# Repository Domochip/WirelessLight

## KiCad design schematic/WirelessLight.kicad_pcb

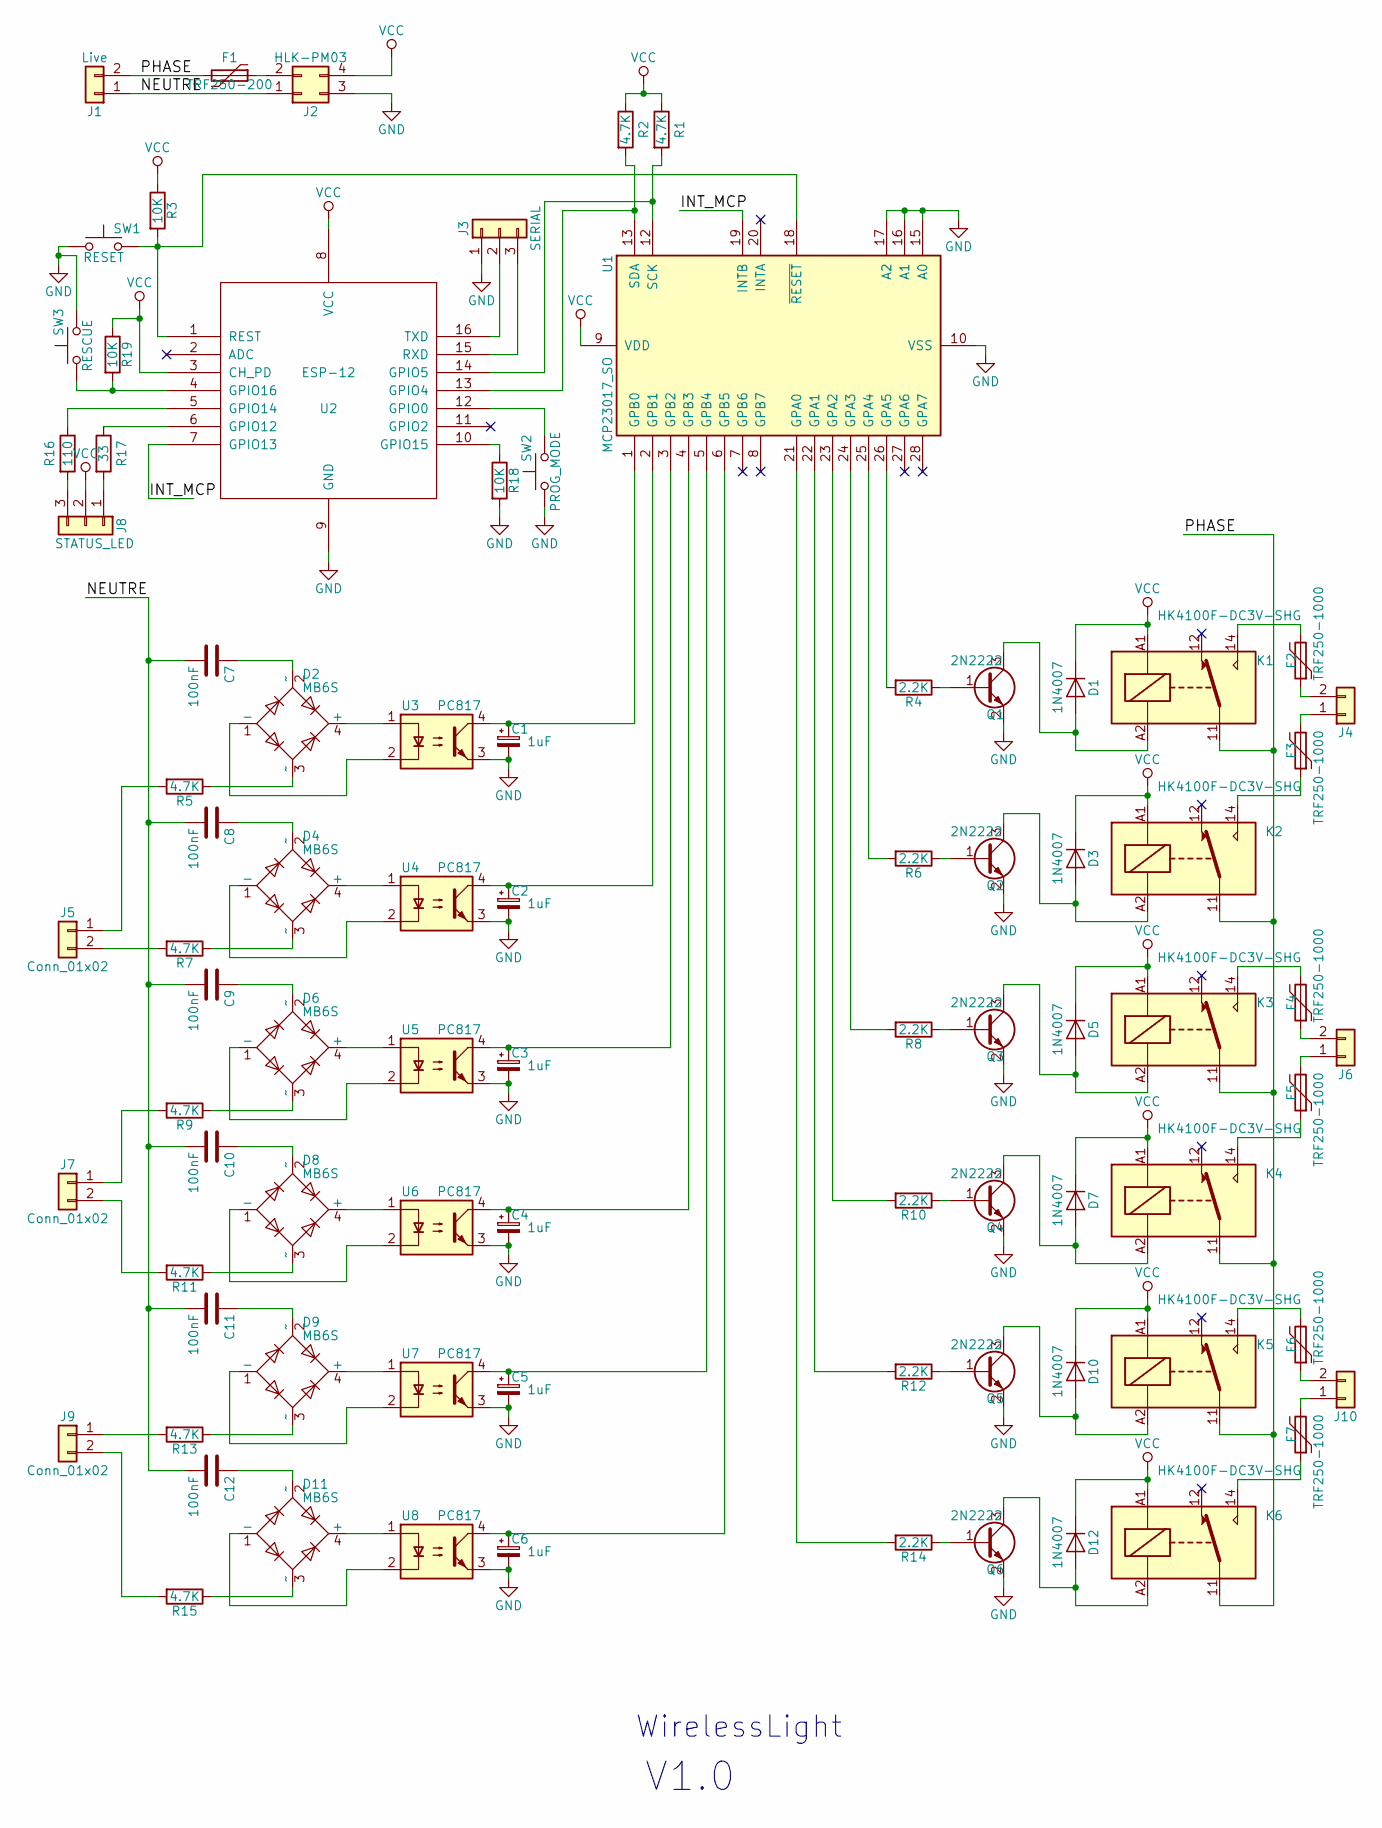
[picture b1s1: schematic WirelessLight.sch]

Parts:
C1, C2, C3, C4, C5, C6: 1uF; C_0805_HandSoldering
C7, C8, C9, C10, C11, C12: 100nF; C_1812_HandSoldering
D1, D3, D5, D7, D10, D12: 1N4007; D_SMA_Handsoldering
D2, D4, D6, D8, D9, D11: MB6S; TO-269AA
F1: TRF250-200; TRF250-400
F2, F3, F4, F5, F6, F7: TRF250-1000
J1: Live; KF235-2P-3.81
J2: HLK-PM03; HLK-PM01
J3: SERIAL; Pin_Header_Straight_1x03_Pitch2.54mm
J4, J5, J6, J7, J9, J10: Conn_01x02; KF235-2P-3.81
J8: STATUS_LED; Pin_Header_Straight_1x03_Pitch2.54mm
K1, K2, K3, K4, K5, K6: HK4100F-DC3V-SHG; HK4100F
Q1, Q2, Q3, Q4, Q5, Q6: 2N2222; SOT-23_Handsoldering
R1, R2: 4.7K; R_0805_HandSoldering
R3, R18, R19: 10K; R_0805_HandSoldering
R4, R6, R8, R10, R12, R14: 2.2K; R_0805_HandSoldering
R5, R7, R9, R11, R13, R15: 4.7K; R_2010_HandSoldering
R16: 110; R_0805_HandSoldering
R17: 33; R_0805_HandSoldering
SW1: RESET; SW_PUSH_6mm_h5mm
SW2: PROG_MODE; SW_PUSH_6mm_h5mm
SW3: RESCUE; SW_PUSH_6mm_h5mm
U1: MCP23017_SO; SOIC-28W_7.5x17.9mm_Pitch1.27mm
U2: ESP-12
U3, U4, U5, U6, U7, U8: PC817; DIP-4_W8.89mm_SMDSocket_LongPads

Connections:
/INT_MCP: U1.19 (INTB), U2.7 (GPIO13)
/NEUTRE: C7.2, C8.2, C9.2, C10.2, C11.2, C12.2, J1.1, J2.1
/PHASE: F1.2, J1.2, K1.11, K2.11, K3.11, K4.11, K5.11, K6.11
GND: C1.2, C2.2, C3.2, C4.2, C5.2, C6.2, J2.3, J3.1, Q1.2 (E), Q2.2 (E), Q3.2 (E), Q4.2 (E), Q5.2 (E), Q6.2 (E), R18.2, SW1.1, SW2.1, SW3.2, U1.10 (VSS), U1.15 (A0), U1.16 (A1), U1.17 (A2), U2.9 (GND), U3.3, U4.3, U5.3, U6.3, U7.3, U8.3
unnamed: C1.1, U1.1 (GPB0), U3.4
unnamed: C2.1, U1.2 (GPB1), U4.4
unnamed: C3.1, U1.3 (GPB2), U5.4
unnamed: C4.1, U1.4 (GPB3), U6.4
unnamed: C5.1, U1.5 (GPB4), U7.4
unnamed: C6.1, U1.6 (GPB5), U8.4
unnamed: C7.1, D2.2 (~~)
unnamed: C8.1, D4.2 (~~)
unnamed: C9.1, D6.2 (~~)
unnamed: C10.1, D8.2 (~~)
unnamed: C11.1, D9.2 (~~)
unnamed: C12.1, D11.2 (~~)
unnamed: D1.2 (A), K1.A2, Q1.3 (C)
unnamed: D2.1 (-), U3.2
unnamed: D2.3 (~~), R5.1
unnamed: D2.4 (+), U3.1
unnamed: D3.2 (A), K2.A2, Q2.3 (C)
unnamed: D4.1 (-), U4.2
unnamed: D4.3 (~~), R7.1
unnamed: D4.4 (+), U4.1
unnamed: D5.2 (A), K3.A2, Q3.3 (C)
unnamed: D6.1 (-), U5.2
unnamed: D6.3 (~~), R9.1
unnamed: D6.4 (+), U5.1
unnamed: D7.2 (A), K4.A2, Q4.3 (C)
unnamed: D8.1 (-), U6.2
unnamed: D8.3 (~~), R11.1
unnamed: D8.4 (+), U6.1
unnamed: D9.1 (-), U7.2
unnamed: D9.3 (~~), R13.1
unnamed: D9.4 (+), U7.1
unnamed: D10.2 (A), K5.A2, Q5.3 (C)
unnamed: D11.1 (-), U8.2
unnamed: D11.3 (~~), R15.1
unnamed: D11.4 (+), U8.1
unnamed: D12.2 (A), K6.A2, Q6.3 (C)
unnamed: F1.1, J2.2
unnamed: F2.1, J4.2
unnamed: F2.2, K1.14
unnamed: F3.1, K2.14
unnamed: F3.2, J4.1
unnamed: F4.1, J6.2
unnamed: F4.2, K3.14
unnamed: F5.1, K4.14
unnamed: F5.2, J6.1
unnamed: F6.1, J10.2
unnamed: F6.2, K5.14
unnamed: F7.1, K6.14
unnamed: F7.2, J10.1
unnamed: J3.2, U2.16 (TXD)
unnamed: J3.3, U2.15 (RXD)
unnamed: J5.1, R5.2
unnamed: J5.2, R7.2
unnamed: J7.1, R9.2
unnamed: J7.2, R11.2
unnamed: J8.1, R17.2
unnamed: J8.3, R16.2
unnamed: J9.1, R13.2
unnamed: J9.2, R15.2
unnamed: Q1.1 (B), R4.1
unnamed: Q2.1 (B), R6.1
unnamed: Q3.1 (B), R8.1
unnamed: Q4.1 (B), R10.1
unnamed: Q5.1 (B), R12.1
unnamed: Q6.1 (B), R14.1
unnamed: R1.2, U1.12 (SCK), U2.14 (GPIO5)
unnamed: R2.2, U1.13 (SDA), U2.13 (GPIO4)
unnamed: R3.2, SW1.2, U1.18 (~RESET~), U2.1 (REST)
unnamed: R4.2, U1.26 (GPA5)
unnamed: R6.2, U1.25 (GPA4)
unnamed: R8.2, U1.24 (GPA3)
unnamed: R10.2, U1.23 (GPA2)
unnamed: R12.2, U1.22 (GPA1)
unnamed: R14.2, U1.21 (GPA0)
unnamed: R16.1, U2.5 (GPIO14)
unnamed: R17.1, U2.6 (GPIO12)
unnamed: R18.1, U2.10 (GPIO15)
unnamed: R19.2, SW3.1, U2.4 (GPIO16)
unnamed: SW2.2, U2.12 (GPIO0)
VCC: D1.1 (K), D3.1 (K), D5.1 (K), D7.1 (K), D10.1 (K), D12.1 (K), J2.4, J8.2, K1.A1, K2.A1, K3.A1, K4.A1, K5.A1, K6.A1, R1.1, R2.1, R3.1, R19.1, U1.9 (VDD), U2.3 (CH_PD), U2.8 (VCC)

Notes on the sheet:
WirelessLight
V1.0

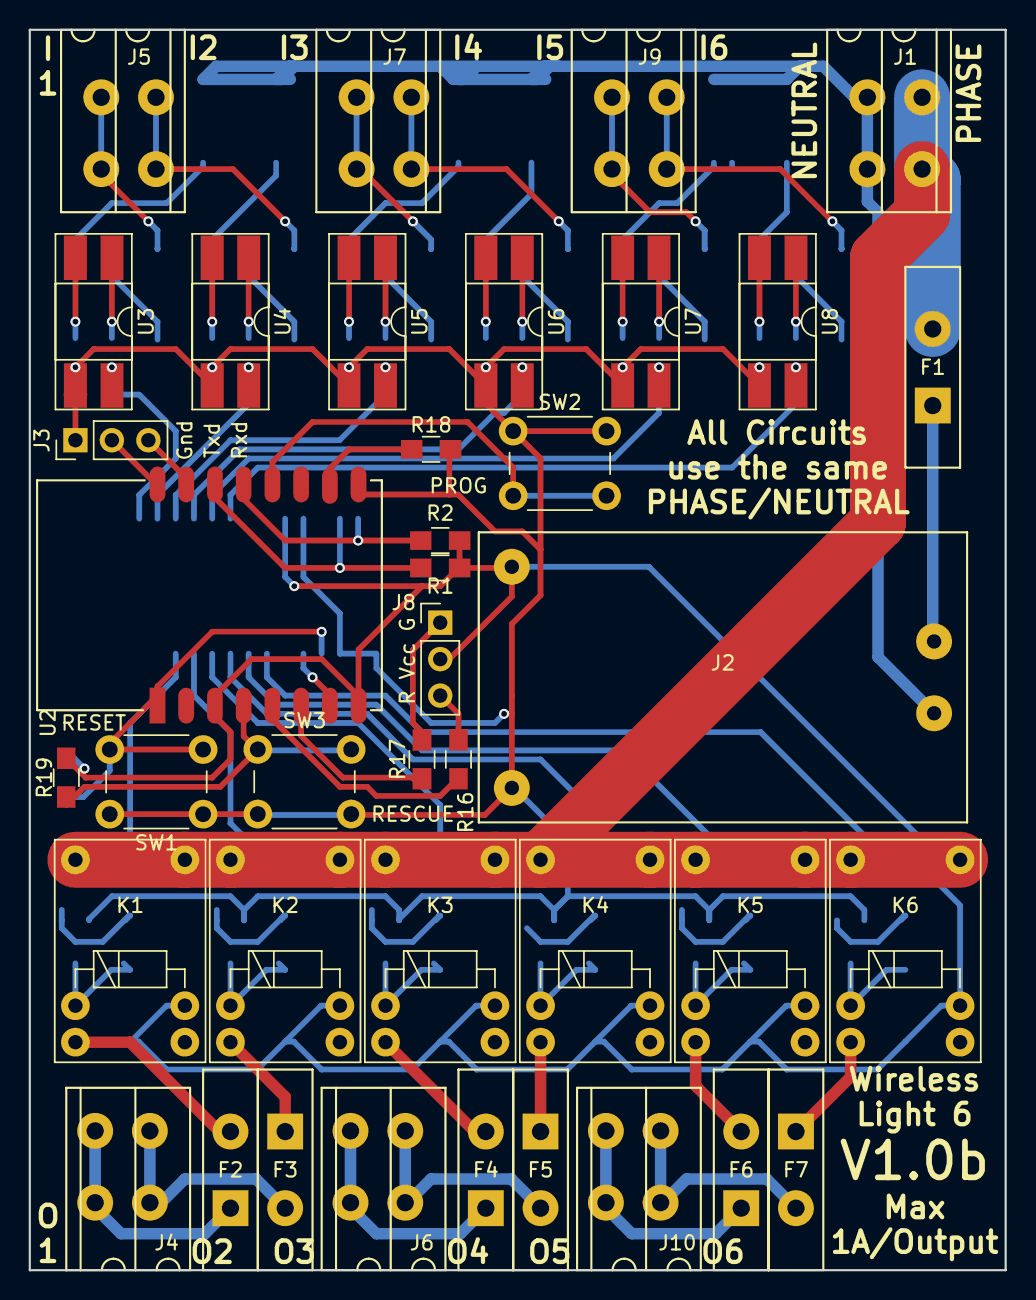
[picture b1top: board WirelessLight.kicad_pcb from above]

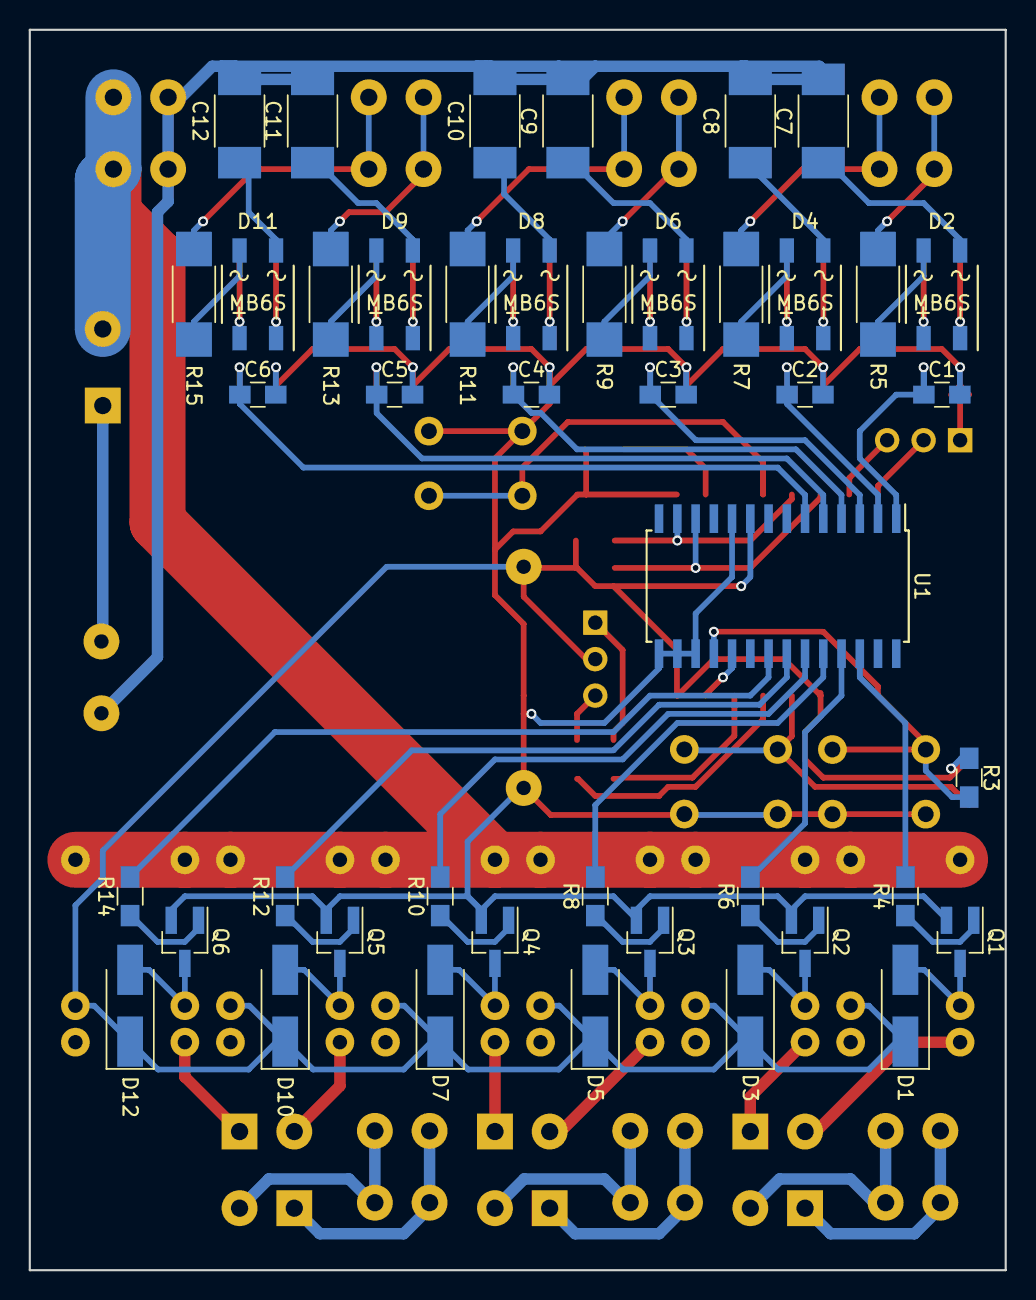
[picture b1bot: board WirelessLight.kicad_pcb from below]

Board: 2 copper layers, 67.9 x 86.4 mm, 83 parts (44 on the bottom side), 84 nets.

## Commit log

2019-03-17 V1.0.7 Initial Commit
2019-03-30 Update to base V1.2.1 Change flash to default size
2019-03-31 V1.0.9 Update to Base V1.2.2 Improve WiFi management
2019-03-31 add include folder
2019-04-02 Update to Base V1.2.3 Improve Wifi
2019-04-05 add library depencies
2019-04-07 PureCSS Fix because of GIT AutoCRLF Windows users enable autocrlf by default, and so pure-min.css crlf modified make bad integrity check
2019-04-13 Improved copy_base.py
2019-04-22 V1.0.10 No TLS for MQTT
2019-04-22 V1.0.11 Improve MQTT management and reconnection
2019-04-22 V1.0.12 better HA status feedback
2019-08-12 Update gitignore
2019-10-13 Compatibility with Python3
2019-10-13 Clean comments
2019-11-03 Up to Base V1.2.7
2019-11-07 Up to base V1.2.8
2019-11-07 replace Serial by LOG_SERIAL
2019-11-07 V1.0.13 Compatibility with Framework 2.5.2!!!
2019-11-16 Up to base V1.3.0
2019-11-17 Up to Base V1.3.1
2019-11-17 Base fix
2019-11-18 Up to Base V1.3.2
2019-11-22 Up to base V1.3.3
2019-11-23 Naming Convention
2019-11-27 Log AP Name
2019-12-10 V1.1.0 improce status1 using EventSource
2020-11-01 Up to base V1.4.0 /!\ Configuration lost after flash /!\
